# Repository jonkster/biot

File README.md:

Experimental code for a sensor network using ATMEL atsamr21g microcontrollers.

#About Biotz

Biotz nodes are small devices that gather and relay data about where they
are physically located (eg their orientation in space, current movement etc).
A group of Biotz nodes can be joined into a network and can provide information
about complex movements of an assembly of parts.

For example, a human body may be
considered as an assembly of various limbs. If a number of Biotz nodes are
attached to locations around the body, the movement of the limbs can be
monitored or recorded.

The prototype Biotz nodes were initially implemented using ATSAMR21ZLL-EK and
ATSAMR21-XPRO boards, the latest version uses an ATSAMR21B-MZ210PA module and
MPU9250 IMU device.

The nodes run a forked version of RIOT OS (see https://github.com/RIOT-OS/RIOT for the 'real' RIOT not my hacked up one). 
My forked version is at https://github.com/jonkster/RIOT and is forked to allow
me to support the (currently) unsupported ATSAMR21ZLL-EK boards, the
ATSAMR21B-MZ210PA module and the MPU9250 IMU device and also some customised
bits I have added to the ATSAMR21-XPRO boards.  NB the coding standard for my
changes is not production quality and shouldn't be pushed back into the 'real'
RIOT without significant refactoring - my stuff is prototype/proof of concept
only!).

The nodes communicate using 6lowPAN with an edge router (currently an
ATSAMR21-ZLLK board with a SLIP network interface to the wider network).  The
edge router is the root of a number of Biotz sensor devices.

This stuff is very experimental and a work in progress.  Code quality (my code anyway) ranges from crap to even worse.  You have been warned. :)

Current Structure
```
├── biot-applications
│   ├── biot - the sensor node code for the ZLL-EK and XPRO boards
│   ├── router - the edge router code
│   ├── modules - components common to the router and sensor nodes
│   └── utils - some stuff to assist flashing and working with the boards (cruddy but handy)
├── biot-broker - a nodejs based web service run on the PC that provides information on the Biotz network to other applications
└── biot-interface - a browser based user interface to the Biotz network

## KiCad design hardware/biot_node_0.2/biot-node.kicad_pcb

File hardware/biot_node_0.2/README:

Attempt to make small PCB but using prebuilt modules for ATSAMR21,  IMU9250,
NCP1402.

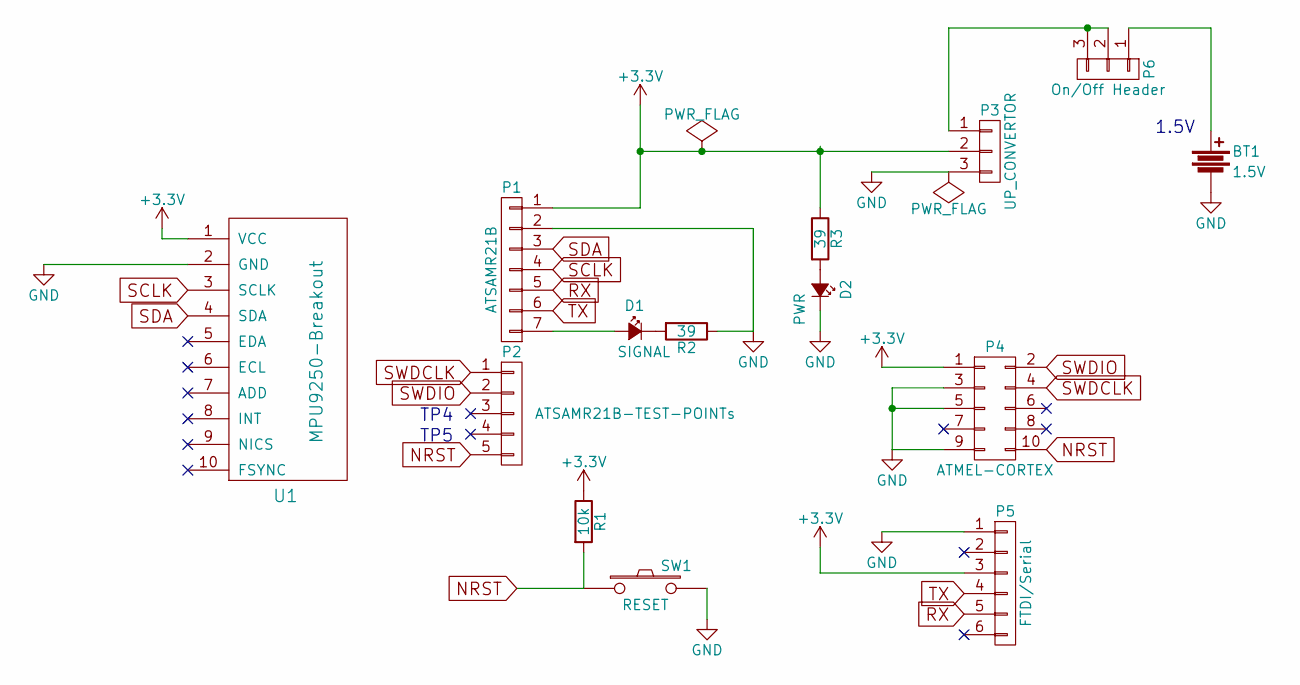
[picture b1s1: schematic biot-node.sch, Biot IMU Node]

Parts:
BT1: 1.5V; AAA_x1_Battery_Holder
D1: SIGNAL; LED_1206
D2: PWR; LED_1206
P1: ATSAMR21B; Pin_Header_Straight_1x07_Pitch2.00mm
P2: ATSAMR21B-TEST-POINTs; Pin_Header_Straight_1x05
P3: UP_CONVERTOR; Pin_Header_Straight_1x03
P4: ATMEL-CORTEX; ATMEL_cortex_header_smd
P5: FTDI/Serial; Pin_Header_Straight_1x06
P6: On/Off Header; Pin_Header_Straight_1x03
R1: 10k; R_1210
R2, R3: 39; R_1210
SW1: RESET; SW_SPST_EVPBF
U1: MPU9250-Breakout; Pin_Header_Straight_1x10

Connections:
+3V3: P1.1, P3.2, P4.1, P5.3, R1.1, R3.1, U1.1 (VCC)
GND: BT1.2, D2.1 (K), P1.2, P3.3, P4.3, P4.5, P4.9, P5.1, R2.1, SW1.2, U1.2 (GND)
NRST: P2.5, P4.10, R1.2, SW1.1
unnamed: BT1.1, P6.1
unnamed: D1.1 (K), R2.2
unnamed: D1.2 (A), P1.7
unnamed: D2.2 (A), R3.2
unnamed: P3.1, P6.2, P6.3
RX: P1.5, P5.5
SCLK: P1.4, U1.3 (SCLK)
SDA: P1.3, U1.4 (SDA)
SWDCLK: P2.1, P4.4
SWDIO: P2.2, P4.2
TX: P1.6, P5.4

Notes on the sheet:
TP4
TP5
1.5V

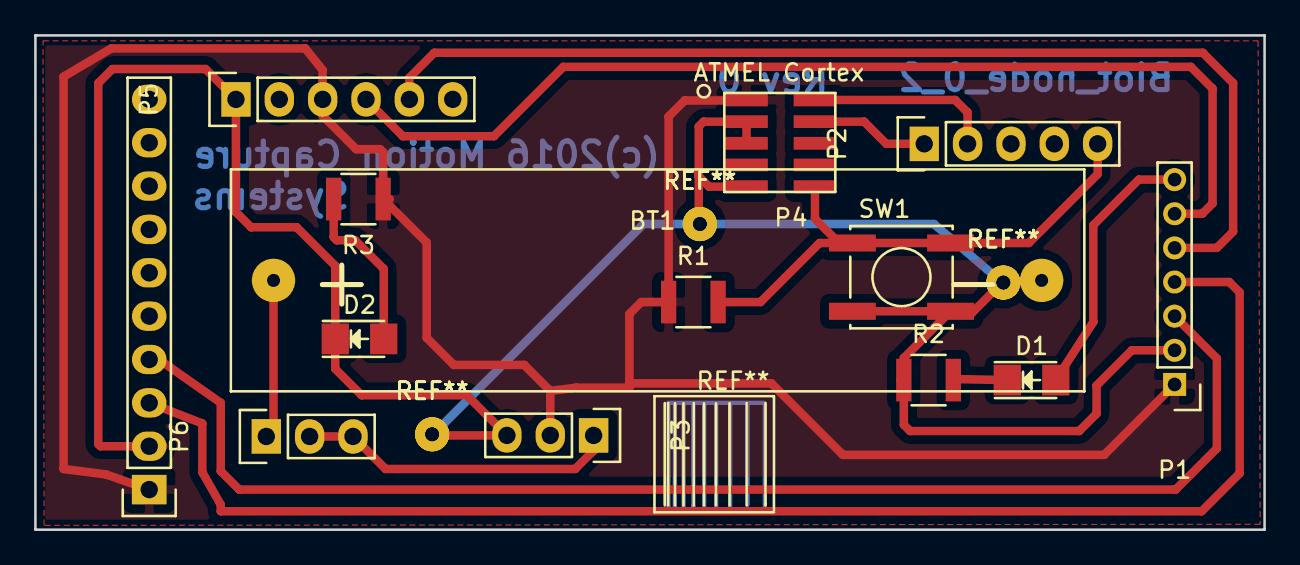
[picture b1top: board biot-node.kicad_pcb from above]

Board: 2 copper layers, 72.0 x 29.0 mm, 14 parts (0 on the bottom side), 14 nets.

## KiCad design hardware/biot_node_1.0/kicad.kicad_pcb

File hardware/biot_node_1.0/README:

Attempt to have MPU9250 and NCP1402 as dicrete components rather than using the
modules.

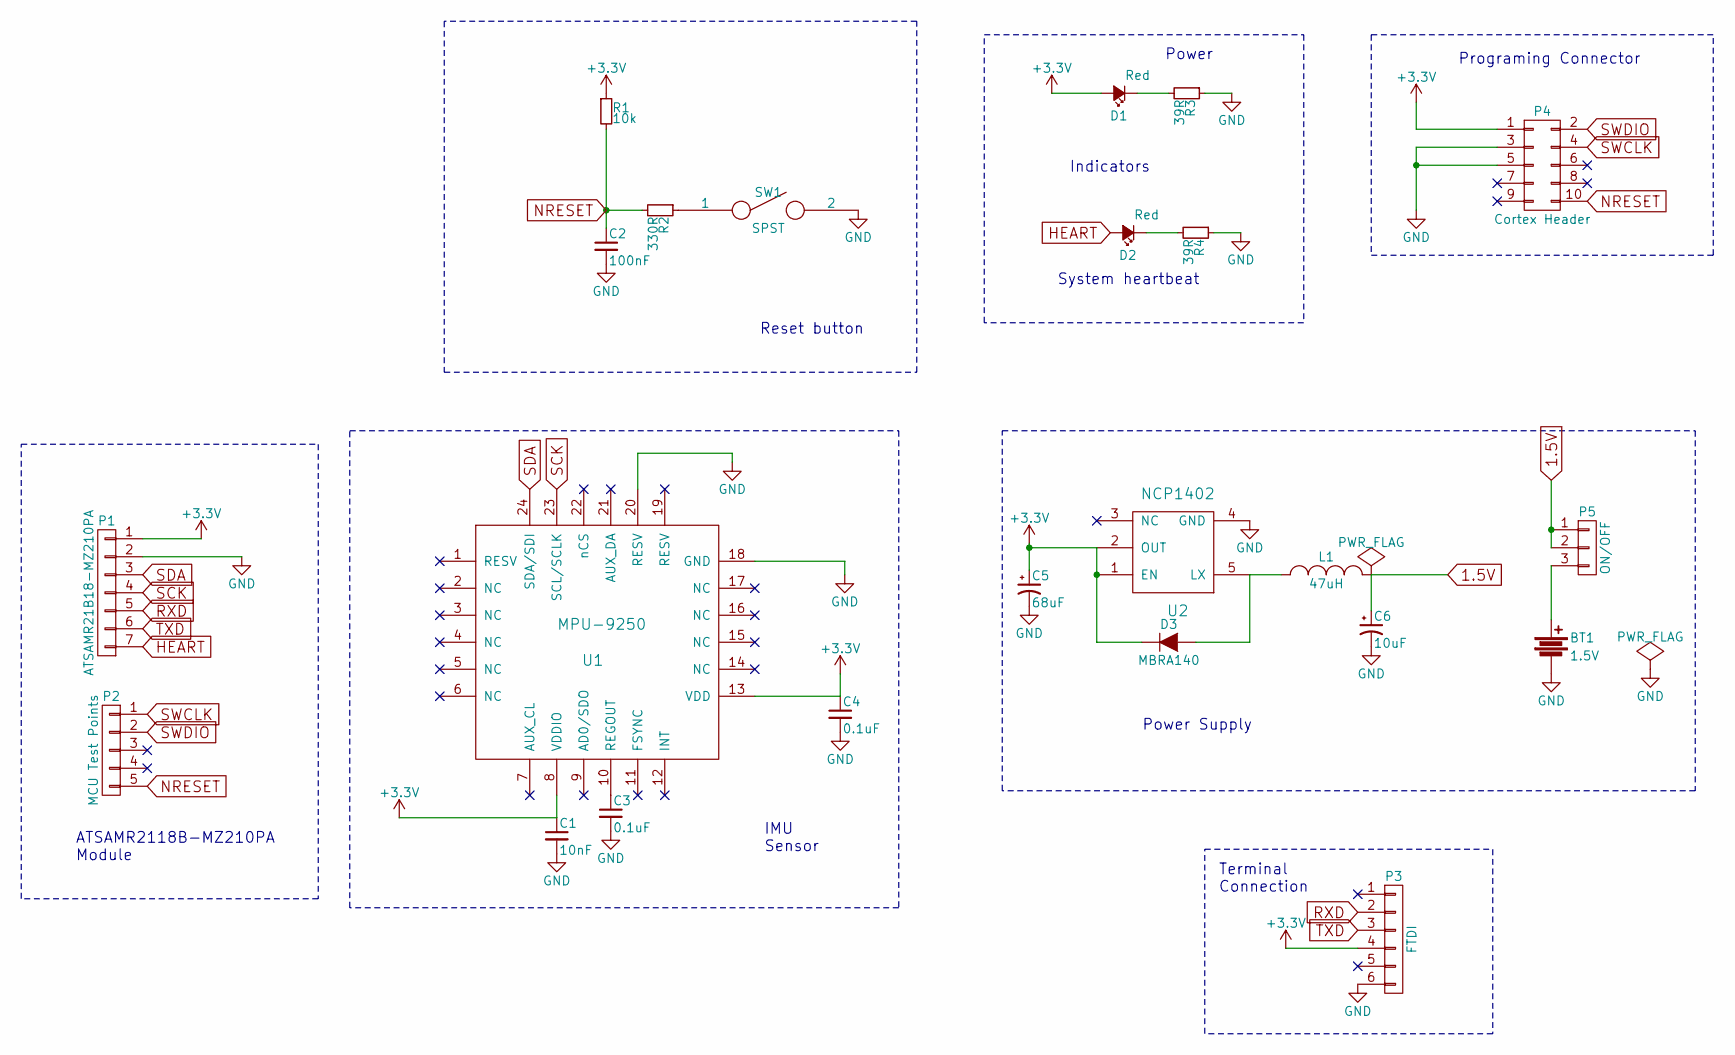
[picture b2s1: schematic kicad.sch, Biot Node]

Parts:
BT1: 1.5V; AAA_x1_Battery_Holder
C1: 10nF; C_1206
C2: 100nF; C_1206
C3, C4: 0.1uF; C_1206
C5: 68uF; C_1206
C6: 10uF; C_1206
D1, D2: Red; LED_1206
D3: MBRA140; DO-214AB
L1: 47uH; Inductor_1212
P1: ATSAMR21B18-MZ210PA; Pin_Header_Straight_1x07_Pitch2.00mm
P2: MCU Test Points; Pin_Header_Straight_1x05
P3: FTDI; Pin_Header_Straight_1x06
P4: Cortex Header; ATMEL_cortex_header_smd
P5: ON/OFF; Pin_Header_Straight_1x03
R1: 10k; R_1210
R2: 330R; R_1210
R3, R4: 39R; R_1210
SW1: SPST; SW_SPST_EVPBF
U1: MPU-9250; QFN-24-1EP_4x4mm_Pitch0.5mm
U2: NCP1402; SOT-23-5

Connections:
1.5V: C6.1, L1.2, P5.1, P5.2
+3V3: C1.1, C4.1, C5.1, D1.2 (A), D3.1 (K), P1.1, P3.4, P4.1, R1.1, U1.8 (VDDIO), U1.13 (VDD), U2.1 (EN), U2.2 (OUT)
GND: BT1.2, C1.2, C2.2, C3.2, C4.2, C5.2, C6.2, P1.2, P3.6, P4.3, P4.5, R3.1, R4.1, SW1.2, U1.18 (GND), U1.20 (RESV), U2.4 (GND)
HEART: D2.2 (A), P1.7
NRESET: C2.1, P2.5, P4.10, R1.2, R2.2
unnamed: BT1.1, P5.3
unnamed: C3.1, U1.10 (REGOUT)
unnamed: D1.1 (K), R3.2
unnamed: D2.1 (K), R4.2
unnamed: D3.2 (A), L1.1, U2.5 (LX)
unnamed: R2.1, SW1.1
RXD: P1.5, P3.2
SCK: P1.4, U1.23 (SCL/SCLK)
SDA: P1.3, U1.24 (SDA/SDI)
SWCLK: P2.1, P4.4
SWDIO: P2.2, P4.2
TXD: P1.6, P3.3

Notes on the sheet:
Indicators
Power
System heartbeat
Programing Connector
Power Supply
Terminal Connection
IMU Sensor
Reset button
ATSAMR2118B-MZ210PA Module

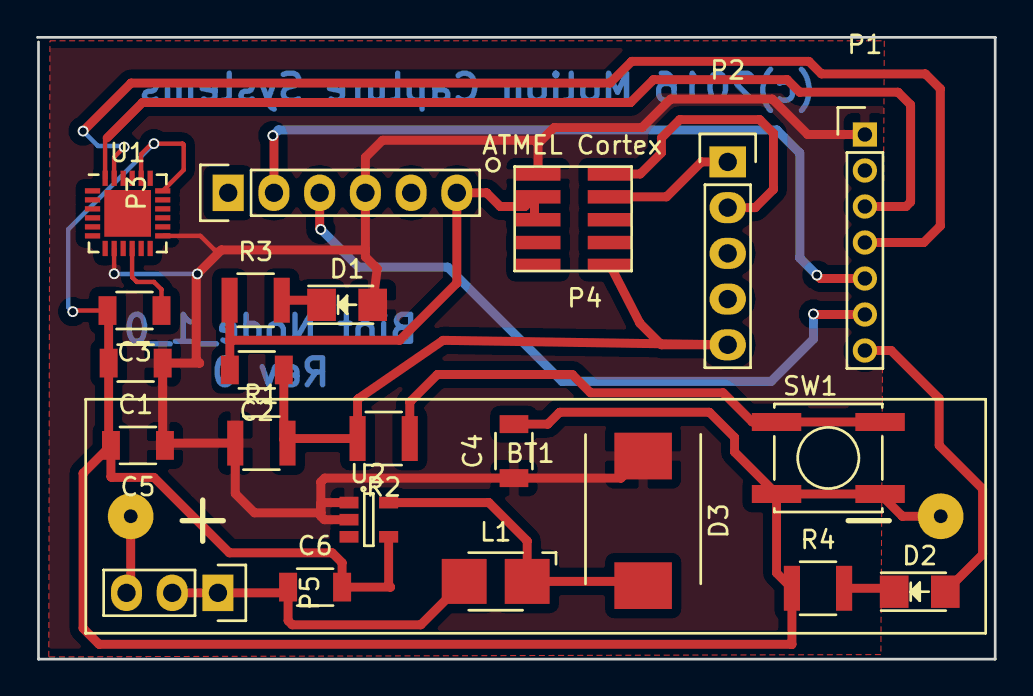
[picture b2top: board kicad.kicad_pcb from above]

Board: 2 copper layers, 53.2 x 34.5 mm, 23 parts (0 on the bottom side), 17 nets.

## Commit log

2016-04-20 Changed path to RIOT in Makefile.
2016-04-25 Added udp network test experiments.
2016-06-22 Added xpro board and getting more accurate ADC measurements.
2016-06-22 Added git ignore.
2016-06-23 Adding OLED I2C stuff.
2016-06-23 Removed ADC check during housekeeping.
2016-06-24 Working on OLED/SPI stuff.
2016-06-27 Working on SPI interface to OLED (not working).
2016-06-27 Made simple working app.
2016-06-27 Working initially.
2016-06-27 Refining OLED display write.
2016-06-28 OLED now working but networking broken.
2016-06-28 Added seperate OLED only project.
2016-06-28 Added seperate utils directory.
2016-06-28 Added OLED project.
2016-06-28 Added better utilities for flashing and terminal access.
2016-06-28 Adding networking experiments.
2016-06-28 Renamed the net example to 'nodes'.
2016-06-28 Added mutex lock for display writing in oled experiments.
2016-06-28 Added 'simplenet' experiment to get basic networking running.
2016-06-28 Trying to get udp and oled working (still not working).
2016-06-29 Added network nodes plus oled experiment (working).
2016-06-29 Making seperate display module component.
2016-06-29 Using module component for display.
2016-06-29 Adding udp comms to oled nodes.
2016-06-29 Updated README.
2016-06-30 Moving display stuff into reusable module.
2016-06-30 Adding samr21-xpro board border router.
2016-06-30 Adding rpl.
2016-06-30 Adding rpl node experiment.
2016-06-30 Adding handling utilities for more nodes.
2016-06-30 Allowing code to be used across zllk and xpro boards.
2016-07-03 Refactored project structure to remove clutter.
2016-07-03 Setting up biot node to be able to be implemented using xpro board as well as zll-ek board.
2016-07-04 Getting time sync working between nodes.
2016-07-05 Improving time coordination between nodes.
2016-07-05 Getting border router SLIP stuff working.
2016-07-05 Adding foundation for node data sending stuff.
2016-07-05 Tidy up router application.
2016-07-05 Starting to add data caching by router.
2016-07-06 Adding ability for router to collate data from nodes.
2016-07-07 Setting up communication of collated node data through router.
2016-07-08 Adding Biot interface/control applications.
2016-07-08 Removed wrong copyright headers.
2016-07-08 Added CORS headers to web service.
2016-07-08 Interfacing to broker to display live data.
2016-07-11 Added ability to identify nodes using web interface.
2016-07-11 Modified nodes to send orientation data (currently simulated movements).
2016-07-11 Added 3D drawing directive.
2016-07-11 Modified interface to display 3D representation of node orientation.
2016-07-11 Trivial changes to mock position generating and to display.
2016-07-11 Make router become route on boot rather than after button press.
2016-07-11 Add control to interface to trigger a node net resync.
2016-07-12 Added quaternion position components.
2016-07-13 Adding experiment with MPU9150 IMU unit.
2016-07-16 Simplified flash and terminal shell scripts.
2016-07-16 Getting i2c interface to IMU MPU9150 device working.
2016-07-16 Adding IMU device interface and changing router to ZLL-EK board from XPRO as the XPRO better for driving I2C devices.
2016-07-16 Making XPRO boards main biot nodes as they have easier I2C interface.
2016-07-19 Display changes to draw better 3d represntation of node.
2016-07-19 Building up direction generation from IMU readings.
2016-07-19 Working on fusion of IMU data.
2016-07-20 Refining IMU data fusion.
2016-07-21 Work on weird memory issue in data caching.
2016-07-21 Fixed memory initialisation error.
2016-07-21 Reintroducing components removed when fixing malloc issues.
2016-07-21 Trying to get calibration passing between nodes and router working.
2016-07-21 Trigger sending calibration from nodes every 10 seconds.
2016-07-21 Minor changes getting udp timeout issue resolved.
2016-07-21 Fixed time coordination bug which also resolves udp timeout bug.
2016-07-21 Updated tunslip6 utility with lower verbosity.
2016-07-22 Fixed memory overflow bug on calibration requests.
2016-07-22 Added calibration type requests to web service.
2016-07-22 Working on node and router stability and robustness.
2016-07-22 Bringing calibration data to user display.
2016-07-22 Working on stability issues.
2016-07-24 Catch invalid json from nodes.
2016-07-24 ALlow restarting of IMU device within node shell.
2016-07-25 Changed broker to be the collator of biotz node data rather than the router.
2016-07-25 Removing need for router to collate node data - now just passes it on.
2016-07-25 Fixed broker not returning correct calibration data.
2016-07-25 Removed caching of node values by router.
2016-07-25 Fixed issue where max magnetometer values weren't returning.
2016-07-25 Adding ability to save and recall magnetometer calibrations.
2016-07-25 Added ignore for data files.
2016-07-26 Added status request methods to API.
2016-07-26 Increased calibration send frequency.
2016-07-26 Added status display and ability for UI to drop unresponsive nodes.
2016-07-26 Adding ability to view single node in UI.
2016-07-26 Improving node visualisation in UI.
2016-07-26 Minor screen layout changes.
2016-07-26 Make axis indicators cast shadows.
2016-07-27 Added ability to send previously saved calibration data to a node.
2016-07-27 Added calibration sending calls to API.
2016-07-27 Added ability to UI to push saved calibrations to nodes.
2016-07-28 Adding ability to selectively control accelerometers/gyros and magnetometers.
2016-07-31 Changes to get accelerometer orientations working.
2016-08-01 Experimental changes to how accelerometer values contribute to orientation.
2016-08-02 IMplemented better fusion algorithm for measuring orientation.
2016-08-05 Changes to fix bug in fusion where calculated orientation jumped off if node moved in certain orientations.
2016-08-08 Refining quaternion calculations.
2016-08-09 Several changes to reduce stack memory usage and also allow finer control over calibration setting.
2016-08-10 Reducing volume of network traffic to improve router stability.
2016-08-10 Adding documentation to assist moving nodes to ATSAMR21B18-MZ210PA board.
2016-08-11 Added makefile for the ATSAMR91B18-MZ210PA board.
2016-08-12 Corrected typos in doc.
2016-08-12 Removed fail on 0 gyro readings as this could be potentially valid.
2016-08-18 Adding MPU9250 IMU device to node.
2016-09-01 Minor updates of README files.
2016-09-09 Started adding kicad hardware and schematic bits.
2016-09-09 Updated .gitignore for hardware.
2016-09-09 Adding kicad files for various incarnations of boards.
2016-09-09 Started to add node assembly user interface.
2016-09-11 More work on node assembling in user interface.
2016-09-13 Adding node assembly functionality in user interface.
2016-09-13 Adding simple dropdown UI control.
2016-09-13 Adding rudimentary limb representation in UI display.
2016-09-13 Added ability to create dummy nodes for testing.
2016-09-15 Simplifying assembly components on user interface.
2016-09-15 Adding ability to save assemblies between sessions.
2016-09-16 Fixing up issues with dummy nodes and allowing limb assemblies to be named.
2016-09-23 Removed duplicate line.
2016-09-23 Added API and architecture documentation.
2016-09-27 Initial changes to add new API spec behaviour to biots and router.
2016-09-28 More changes to implement new API in biots/router.
2016-09-28 Changes to make experiment code work after RIOT changes.
2016-09-29 Fixed issue with ZLLK board crashing when shell started.
2016-09-29 More new API functionality.
2016-09-30 Adding new API calls to components.
2016-09-30 Adding more API functionality.
2016-09-30 Updating interface to use new API.
2016-10-04 Added temporary messages to IMU code for debugging.
2016-10-04 Fixed compiler warning.
2016-10-04 Removed debugging messages.
2016-10-13 Adding more API changes.
2016-10-13 Minor updates to API specification.
2016-10-14 Adding latest Biot Node PCB files.
2016-10-17 Changed Makefile to use default node microcontroller.
2016-10-17 Adding 'Poke' command to system.
2016-10-20 Removed dummy response block.
2016-10-20 Fixed syntax error.
2016-10-20 Minor code layout change.
2016-10-27 Moving interface to newer Angular2 environment.
2016-10-27 Adding functionality to user interface.
2016-10-28 Allowing better scene rotation by user.
2016-10-28 Adding ability to draw labels on display.
2016-10-28 Minor HTML mods.
2016-10-28 Lengthened world axis on display.
2016-10-28 Refining IMU fusion parameters.
2016-10-28 Minor interface layout changes.
2016-10-30 Added orientation labels and fixed parent quaternion undo bug.
2016-10-30 Working on more up to date node status communication.

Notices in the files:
hardware/biot_node_0.2/biot-node.kicad_pcb:
(c)2016 Motion Capture
hardware/biot_node_0.2/biot-node.sch:
Motion Capture Systems (c)2016
hardware/biot_node_1.0/kicad.kicad_pcb:
(c)2016 Motion Capture Systems
